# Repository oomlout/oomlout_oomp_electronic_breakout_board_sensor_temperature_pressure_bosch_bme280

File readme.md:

# Oomp Electronic Project Ibbc Breakout Board Sensor Temperature Pressure Bosch Bme280
Working on an I2C breakout board for the Bosch BME280 temperature, humidity and pressure sensor.
##notes
* none for now
Working on an I2C breakout board for the Bosch BME280 temperature, humidity and pressure sensor.  
* ibom github: [ibom github](kicad/current_version/working/bom/ibom.html)
* ibom direct: [ibom direct](https://raw.githack.com/oomlout/oomlout_oomp_electronic_project_ibbc_breakout_board_sensor_temperature_pressure_bosch_bme280/main/kicad/current_version/working/bom/ibom.html)

## schematic  
  
[schematic (pdf)](kicad/current_version/working/working_schematic.pdf)  

## pcb  

[board (pdf)](kicad/current_version/working/working.pdf)  

## corel working

## oomp_parts_summary
| index | designator | quantity | oomp_id | 
| --- | --- | --- | --- | 
| 1 | C2,C1 | 2 | [electronic_capacitor_0603_100_nano_farad](https://github.com/oomlout/oomlout_oomp_part_src/tree/main/parts/electronic_capacitor_0603_100_nano_farad/working)<br>[c6nf100](https://github.com/oomlout/oomlout_oomp_part_src/tree/main/parts/electronic_capacitor_0603_100_nano_farad/working)<br>[Electronic Capacitor 0603 100 Nano Farad](https://github.com/oomlout/oomlout_oomp_part_src/tree/main/parts/electronic_capacitor_0603_100_nano_farad/working)<br>[LCSC - C14663<br>](https://lcsc.com/product-detail/C14663.html)[LCSC - C30926<br>](https://lcsc.com/product-detail/C30926.html)<br>[Samsung - CL10B104KB8NNNC](https://product.samsungsem.com/mlcc/CL10B104KB8NNN.do) [(L)  ](https://www.lcsc.com/search?q=CL10B104KB8NNNC)[(D)  ](https://www.digikey.com/en/products?keywords=CL10B104KB8NNNC)[(M)  ](https://www.mouser.com/Search/Refine?Keyword=CL10B104KB8NNNC)[(N)  ](https://www.newark.com/search?st=CL10B104KB8NNNC)[(SZ)  ](https://so.szlcsc.com/global.html?k=CL10B104KB8NNNC)<br>[Yageo - CC0603KRX7R9BB104](https://www.yageo.com/en/Chart/Download/pdf/CC0603KRX7R9BB104) [(L)  ](https://www.lcsc.com/search?q=CC0603KRX7R9BB104)[(D)  ](https://www.digikey.com/en/products?keywords=CC0603KRX7R9BB104)[(M)  ](https://www.mouser.com/Search/Refine?Keyword=CC0603KRX7R9BB104)[(N)  ](https://www.newark.com/search?st=CC0603KRX7R9BB104)[(SZ)  ](https://so.szlcsc.com/global.html?k=CC0603KRX7R9BB104)<br> | 
| 2 | R3 | 1 | [electronic_resistor_0603_4700_ohm](https://github.com/oomlout/oomlout_oomp_part_src/tree/main/parts/electronic_resistor_0603_4700_ohm/working)<br>[r6o472](https://github.com/oomlout/oomlout_oomp_part_src/tree/main/parts/electronic_resistor_0603_4700_ohm/working)<br>[Electronic Resistor 0603 4700 Ohm](https://github.com/oomlout/oomlout_oomp_part_src/tree/main/parts/electronic_resistor_0603_4700_ohm/working)<br><br>[Uniroyal - 0603WAJ0472T5E- not in jlc basic parts]() [(L)  ](https://www.lcsc.com/search?q=0603WAJ0472T5E)[(D)  ](https://www.digikey.com/en/products?keywords=0603WAJ0472T5E)[(M)  ](https://www.mouser.com/Search/Refine?Keyword=0603WAJ0472T5E)[(N)  ](https://www.newark.com/search?st=0603WAJ0472T5E)[(SZ)  ](https://so.szlcsc.com/global.html?k=0603WAJ0472T5E)<br>[Uniroyal - 0603WAF4701T5E- jlc basic part]() [(L)  ](https://www.lcsc.com/search?q=0603WAF4701T5E)[(D)  ](https://www.digikey.com/en/products?keywords=0603WAF4701T5E)[(M)  ](https://www.mouser.com/Search/Refine?Keyword=0603WAF4701T5E)[(N)  ](https://www.newark.com/search?st=0603WAF4701T5E)[(SZ)  ](https://so.szlcsc.com/global.html?k=0603WAF4701T5E)<br>[Yageo - RC0603JR-074K7L- available everywhere](https://www.yageo.com/en/Chart/Download/pdf/RC0603JR-074K7L) [(L)  ](https://www.lcsc.com/search?q=RC0603JR-074K7L)[(D)  ](https://www.digikey.com/en/products?keywords=RC0603JR-074K7L)[(M)  ](https://www.mouser.com/Search/Refine?Keyword=RC0603JR-074K7L)[(N)  ](https://www.newark.com/search?st=RC0603JR-074K7L)[(SZ)  ](https://so.szlcsc.com/global.html?k=RC0603JR-074K7L)<br> | 
| 3 | U1 | 1 | [electronic_ic_lga_8_pin_2_5_mm_x_2_5_mm_sensor_pressure_temperature_bosch_bme280](https://github.com/oomlout/oomlout_oomp_part_src/tree/main/parts/electronic_ic_lga_8_pin_2_5_mm_x_2_5_mm_sensor_pressure_temperature_bosch_bme280/working)<br>[isnpt280](https://github.com/oomlout/oomlout_oomp_part_src/tree/main/parts/electronic_ic_lga_8_pin_2_5_mm_x_2_5_mm_sensor_pressure_temperature_bosch_bme280/working)<br>[Electronic Ic Lga 8 Pin 2 5 Mm X 2 5 Mm Sensor Pressure Temperature Bosch Bme280](https://github.com/oomlout/oomlout_oomp_part_src/tree/main/parts/electronic_ic_lga_8_pin_2_5_mm_x_2_5_mm_sensor_pressure_temperature_bosch_bme280/working)<br><br> | 
| 4 | U2 | 1 | [electronic_interposer_soic_14_wide_i2c_helicopter](https://github.com/oomlout/oomlout_oomp_part_src/tree/main/parts/electronic_interposer_soic_14_wide_i2c_helicopter/working)<br>[insoic14wi2cheli](https://github.com/oomlout/oomlout_oomp_part_src/tree/main/parts/electronic_interposer_soic_14_wide_i2c_helicopter/working)<br>[Electronic Interposer Soic 14 Wide I2C Helicopter](https://github.com/oomlout/oomlout_oomp_part_src/tree/main/parts/electronic_interposer_soic_14_wide_i2c_helicopter/working)<br><br> | 
| 5 | CONN1 | 1 | [electronic_header_1_mm_jst_sh_4_pin_surface_mount_right_angle](https://github.com/oomlout/oomlout_oomp_part_src/tree/main/parts/electronic_header_1_mm_jst_sh_4_pin_surface_mount_right_angle/working)<br>[h4psmra](https://github.com/oomlout/oomlout_oomp_part_src/tree/main/parts/electronic_header_1_mm_jst_sh_4_pin_surface_mount_right_angle/working)<br>[Electronic Header 1 Mm Jst Sh 4 Pin Surface Mount Right Angle](https://github.com/oomlout/oomlout_oomp_part_src/tree/main/parts/electronic_header_1_mm_jst_sh_4_pin_surface_mount_right_angle/working)<br>[LCSC - C145956<br>](https://lcsc.com/product-detail/C145956.html)[LCSC - C2906270<br>](https://lcsc.com/product-detail/C2906270.html)<br>[JST - SM04B-SRSS-TB](https://www.jst-mfg.com/product/index.php?series=231) [(L)  ](https://www.lcsc.com/search?q=SM04B-SRSS-TB)[(D)  ](https://www.digikey.com/en/products?keywords=SM04B-SRSS-TB)[(M)  ](https://www.mouser.com/Search/Refine?Keyword=SM04B-SRSS-TB)[(N)  ](https://www.newark.com/search?st=SM04B-SRSS-TB)[(SZ)  ](https://so.szlcsc.com/global.html?k=SM04B-SRSS-TB)<br> | 

Search Links: (L) - lcsc, (D) - digikey, (M) - mouser, (N) - newark, (SZ) - szlcsc
note: a work on progress that takes the bom file from kicad pcb and try's to add oomp details

## positions
### top
| # Ref | Val | Package | PosX | PosY | Rot | Side | 
| --- | --- | --- | --- | --- | --- | --- | 
| C1 | c6nf100 | c6nf100_electronic_capacitor_0603_100_nano_farad | 0.0 | 2.5 | 0.0 | top | 
| C2 | c6nf100 | c6nf100_electronic_capacitor_0603_100_nano_farad | -3.0 | 3.0 | 90.0 | top | 
| R3 | r6o472 | r6o472_electronic_resistor_0603_4700_ohm | -2.0 | -2.5 | 180.0 | top | 
| U1 | isnpt280 | isnpt280_electronic_ic_lga_8_pin_2_5_mm_x_2_5_mm_sensor_pressure_temperature_bosch_bme280 | -0.025 | 0.025 | -90.0 | top | 

### bottom
| # Ref | Val | Package | PosX | PosY | Rot | Side | 
| --- | --- | --- | --- | --- | --- | --- | 
| CONN1 | h4psmra | h4psmra_electronic_header_1_mm_jst_sh_4_pin_surface_mount_right_angle | 0.0 | 1.04 | -90.0 | bottom | 
| U2 | insoic14wi2cheli | insoic14wi2cheli_electronic_interposer_soic_14_wide_i2c_helicopter | 0.0 | 0.0 | 180.0 | bottom |

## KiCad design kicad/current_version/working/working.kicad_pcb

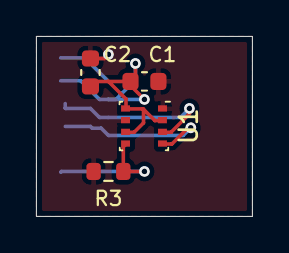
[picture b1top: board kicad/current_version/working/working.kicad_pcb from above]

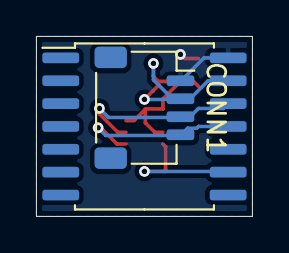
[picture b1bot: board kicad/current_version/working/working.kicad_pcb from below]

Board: 2 copper layers, 12.0 x 10.0 mm, 6 parts (2 on the bottom side), 5 nets.

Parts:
C1, C2: c6nf100; c6nf100_electronic_capacitor_0603_100_nano_farad
CONN1: h4psmra; h4psmra_electronic_header_1_mm_jst_sh_4_pin_surface_mount_r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
R3: r6o472; r6o472_electronic_resistor_0603_4700_ohm
U1: isnpt280; isnpt280_electronic_ic_lga_8_pin_2_5_mm_x_2_5_mm_sensor_pre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
U2: insoic14wi2cheli; insoic14wi2cheli_electronic_interposer_soic_14_wide_i2c_hel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

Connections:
+3V3: C1.1, C2.1, CONN1.3, U1.2 (CSB), U1.6 (VDDIO), U1.8 (VDD), U2.13 (___3v3)
/address: R3.1, U1.5 (SDO), U2.9 (___address)
/scl_3v3: CONN1.1, U1.4 (SCK), U2.11 (___scl_3v3)
/sda_3v3: CONN1.2, U1.3 (SDI), U2.12 (___sda_3v3)
GND: C1.2, C2.2, CONN1.4, R3.2, U1.1 (GND), U1.7 (GND), U2.14 (___gnd)

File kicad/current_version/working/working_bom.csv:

"Id";"Designator";"Footprint";"Quantity";"Designation";"Supplier and ref";
1;"C2,C1";"c6nf100_electronic_capacitor_0603_100_nano_farad";2;"c6nf100";;;
2;"R3";"r6o472_electronic_resistor_0603_4700_ohm";1;"r6o472";;;
3;"U1";"isnpt280_electronic_ic_lga_8_pin_2_5_mm_x_2_5_mm_sensor_pressure_temperature_bosch_bme280";1;"isnpt280";;;
4;"U2";"insoic14wi2cheli_electronic_interposer_soic_14_wide_i2c_helicopter";1;"insoic14wi2cheli";;;
5;"CONN1";"h4psmra_electronic_header_1_mm_jst_sh_4_pin_surface_mount_right_angle";1;"h4psmra";;;

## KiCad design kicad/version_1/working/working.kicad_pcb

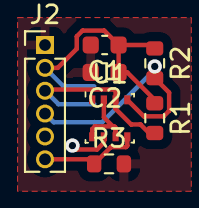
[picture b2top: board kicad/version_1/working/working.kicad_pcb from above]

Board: 2 copper layers, 8 parts (1 on the bottom side), 5 nets.

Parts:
C1, C2: c6nf100; c6nf100_electronic_capacitor_0603_100_nano_farad
J1: h4psmra; h4psmra_electronic_header_1_mm_jst_sh_4_pin_surface_mount_r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
J2: h1d276p; h1d276p_electronic_header_1d27_mm_6_pin
R1, R2, R3: r6o472; r6o472_electronic_resistor_0603_4700_ohm
U1: isn280; isn280_electronic_ic_lga_2_5_mm_x_2_5_mm_8_pin_sensor_press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

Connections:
+3V3: C1.1, C2.1, J1.2, J2.2, R1.1, R2.1, U1.2 (CSB), U1.6 (VDDIO), U1.8 (VDD)
/address: J2.6, R3.1, U1.5 (SDO)
/scl_3v3: J1.4, J2.4, R2.2, U1.4 (SCK)
/sda_3v3: J1.3, J2.3, R1.2, U1.3 (SDI)
GND: C1.2, C2.2, J1.1, J2.1, R3.2, U1.1 (GND), U1.7 (GND)

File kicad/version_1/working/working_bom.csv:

"Id";"Designator";"Footprint";"Quantity";"Designation";"Supplier and ref";
1;"C2,C1";"c6nf100_electronic_capacitor_0603_100_nano_farad";2;"c6nf100";;;
2;"U1";"isn280_electronic_ic_lga_2_5_mm_x_2_5_mm_8_pin_sensor_pressure_temperature_bosch_bme280";1;"isn280";;;
3;"R1,R3,R2";"r6o472_electronic_resistor_0603_4700_ohm";3;"r6o472";;;
4;"J2";"h1d276p_electronic_header_1d27_mm_6_pin";1;"h1d276p";;;
5;"J1";"h4psmra_electronic_header_1_mm_jst_sh_4_pin_surface_mount_right_angle";1;"h4psmra";;;

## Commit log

2023-09-03 initial
2023-09-03 added generations
2023-09-03 schematic update
2023-09-03 commiting after auto generation
2023-09-04 ready to order boards
